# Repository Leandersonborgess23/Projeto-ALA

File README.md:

# Projeto-ALA
Repositório criado por Leanderson Borges para armazenar as informações, dados e conteúdo do projeto ALA.

O projeto ALA (Automatização das Luzes do Auditório) é um projeto de extensão que insiste na implementação automática do jogo de luzes do auditório do IFRN campus Ceará-Mirim, isso através da criação de um hardware, firmware e um software, onde podemos regular a intensidade da luz.

O projeto tem participação dos alunos de INFO3M: Leanderson Borges, Diógenes Santiago e Miguel Carlos. E tem como orientador o docente: Lennedy Campos Soares.

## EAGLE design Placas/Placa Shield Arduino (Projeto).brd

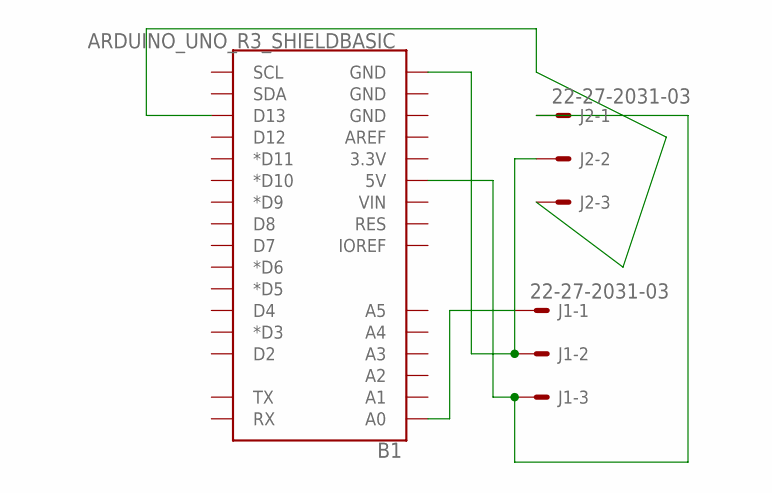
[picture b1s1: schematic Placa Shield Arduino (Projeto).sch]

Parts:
B1: ARDUINO_UNO_R3_SHIELDBASIC; UNO_R3_SHIELD
J1, J2: 22-27-2031-03; 6410-03

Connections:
unnamed: B1.GND@0 (GND), J1.2, J2.2
unnamed: B1.5V, J1.3, J2.1
unnamed: B1.A0, J1.1
unnamed: B1.D13, J2.3

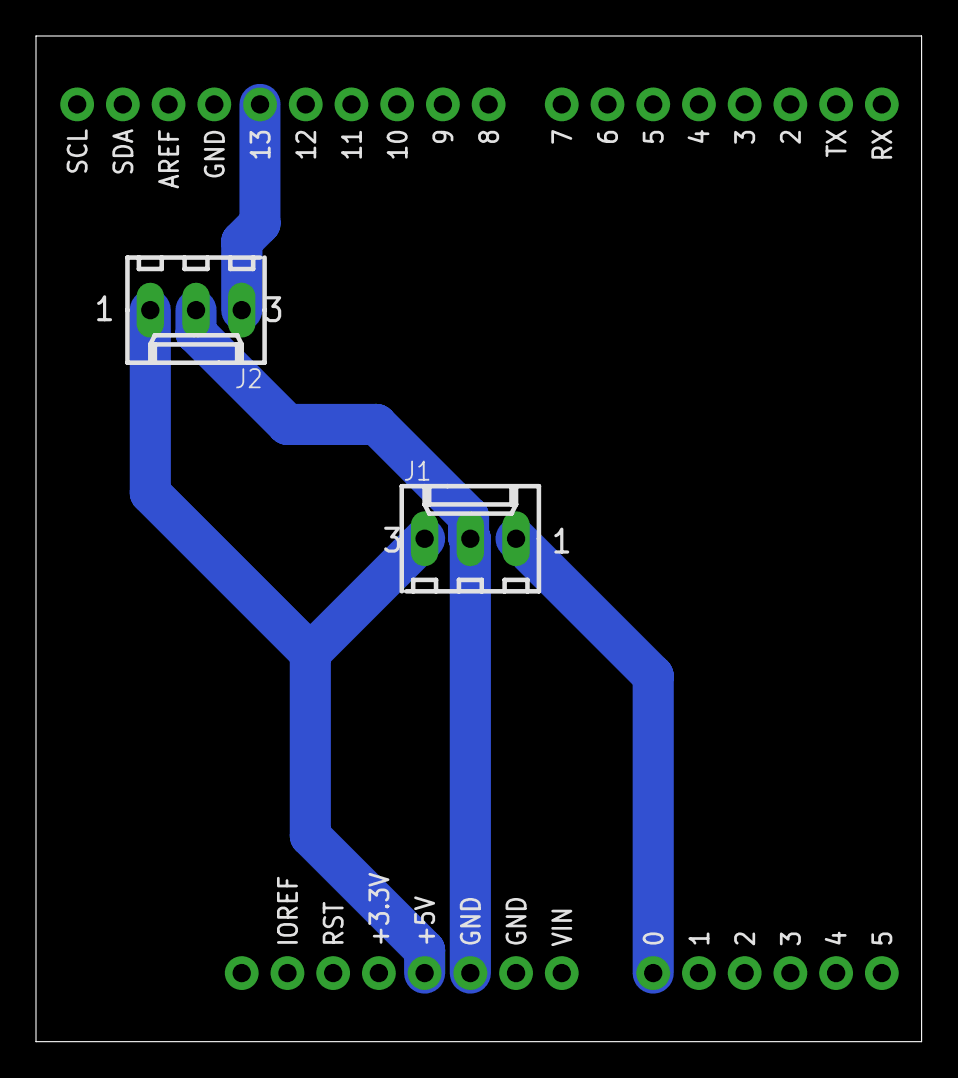
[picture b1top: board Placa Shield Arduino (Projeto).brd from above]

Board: 2 copper layers, 49.2 x 55.9 mm, 3 parts (0 on the bottom side), 4 nets.

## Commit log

2024-12-02 atualização
2025-01-30 cod base para ligar e desligar
2025-01-30 teste onda 1 e 0

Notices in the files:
parts and their libraries:
SparkFun-Boards: Licensing: Creative Commons ShareAlike 4.0 International - https://creativecommons.org/licenses/by-sa/4.0
